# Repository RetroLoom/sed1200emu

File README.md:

# SED1200Emu
This Emulator is intended to replace hard-to-obtain Epson SED1200 based LCD modules with common HD44780 ones. The original project page can be found here http://sensi.org/~tnt23/sed1200emu/index.html. The original goal is for having a replacement LCD for the Roland MT-32, but the display could be adapted for other projects. All attempts to reach the original designer have failed. Please reach out to me if you have any information about this. 

## Building and Installation
The main driver and translator for this project is an ATMEGA8L-8AU which can still be purchased on popular sites like Mouser and Digi-key. This IC may become obsolete, so the intention is to adapt as they become less available. The gerber files, BOM, Binary HEX files will also be provided as they become current and available. All current releases are in beta, and come with no warranty. 

### ATMEGA8 Flashing
When programming the ATMEGA8 it is important to use the correct configuration. This will enable the external clocks and any other flags needed for binary to run correctly. 

Fuse Low Byte: 0xBF

Fuse High Bte: 0xD9

Lock Bit Byte: 0xFF

### Compiling
Download and install WinAVR for minimum compiling support. Using command prompt or windows powershell, run make in the src directory.

Note: You can optionally replace the AVR compiling files to manually update to newer versions. 

### UART Config
For debugging or logging display message, connect via serial to GND, TXD, RXD at 9600 baud.

UART Serial out display clone (and debugging).

### Optional Headers
There are three headers that are considered optional, but recommended if you are developing or want to reprogram the ATMEGA8 after it is soldered to the board. The SPI header will provide connection for flashing, and the UART header will give you access to feedback and debug information for code development. 

## Development Notes
At the moment, 20x2 HD44780 LCD is too large as a direct replacement for the MT-32. Adaptation will be needed in the form of a redesigned 3D printed face plate for the current LCD. If you have interest in helping design something like this, please get in touch! I have searched around for better fitting 20x2 LCD's but I have not found anything that would match. 

Another option is to program new methods that adapts the display to a 16x2 LCD. This might need some elaborate programming to work. 

## License Information
The original release this project is derived from Tim Tashpulatov without license or warranty. The updated revisions of this project released in 2024 include a GPL v3 license which can be found here in the LICENSE file. 

Source code and software license - [GPL v3](https://github.com/skadarnold/sed1200emu/blob/master/LICENSE)

Hardware design license - [CERN OHL-S](https://ohwr.org/project/cernohl/-/wikis/uploads/819d71bea3458f71fba6cf4fb0f2de6b/cern_ohl_s_v2.txt)

## Support the Developer
This project is brought to you free and open source, but it is not free to develop. If you like this project please consider supporting this and future developments. 

https://www.patreon.com/RetroLoom

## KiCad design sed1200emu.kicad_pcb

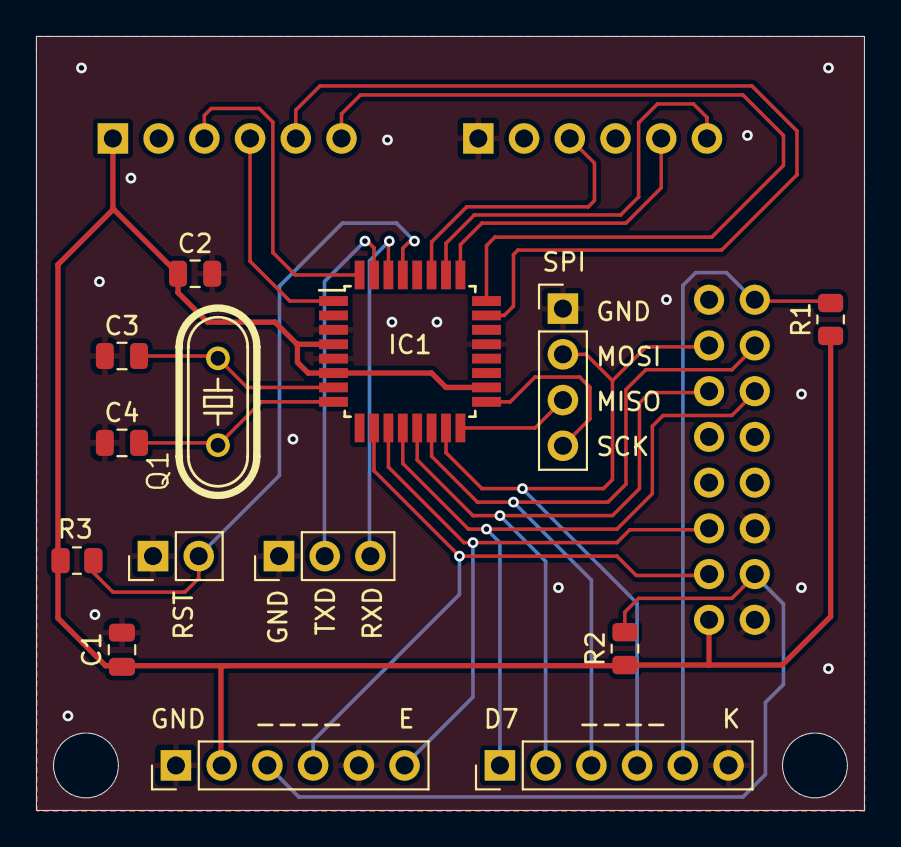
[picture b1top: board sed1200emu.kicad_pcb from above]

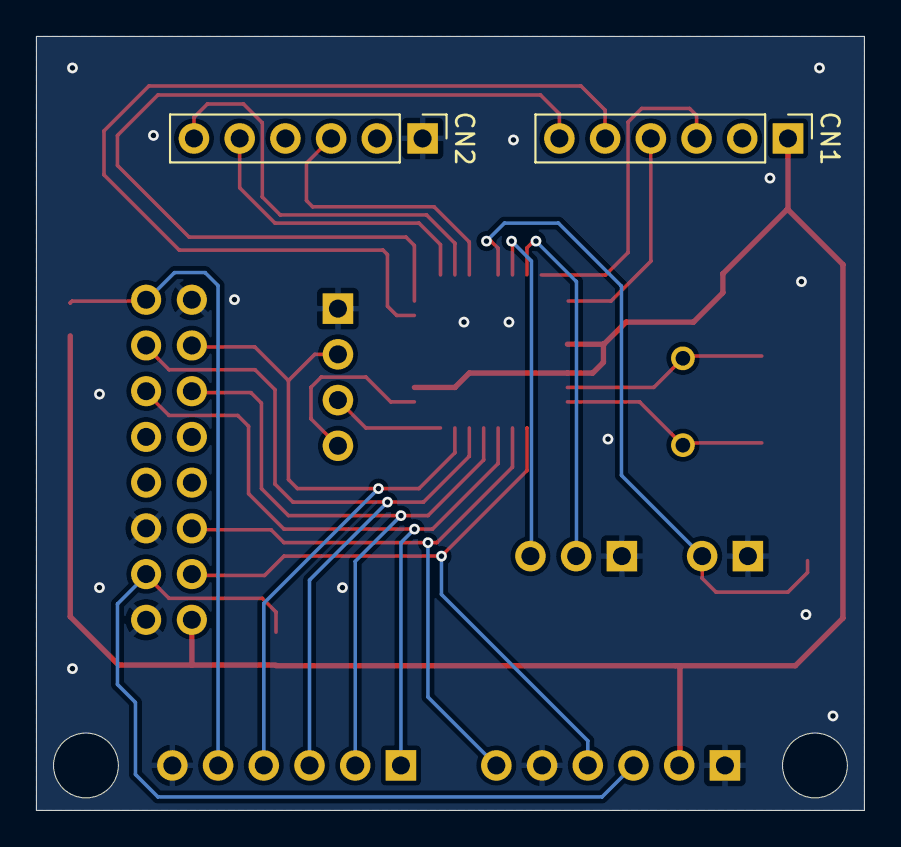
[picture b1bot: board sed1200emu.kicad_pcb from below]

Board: 2 copper layers, 46.0 x 43.0 mm, 17 parts (2 on the bottom side), 24 nets.

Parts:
C1, C2: 0.1uF; C_0805_2012Metric
C3, C4: 22p; C_0805_2012Metric
CN1, CN2: Conn_01x06_Pin 2.54mm; PinHeader_1x06_P2.54mm_Vertical
DIS1: SMH2002-A; TUXGR_20X2
DIS2-1, DIS2-2: Conn_01x06_Pin; PinHeader_1x06_P2.54mm_Vertical
IC1: ATMEGA8L-8AU; TQFP-32_7x7mm_P0.8mm
Q1: HC-49/S 16pF; HC49_S
R1, R2: 330; R_0805_2012Metric
R3: 10k; R_0805_2012Metric
RESET1: Conn_01x02_Pin; PinHeader_1x02_P2.54mm_Vertical
SPI1: Conn_01x04_Pin; PinHeader_1x04_P2.54mm_Vertical
UART1: Conn_01x03_Pin; PinHeader_1x03_P2.54mm_Vertical

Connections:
/ADC0: CN1.5, IC1.23 (PC0(ADC0))
/ADC1: CN1.6, IC1.24 (PC1(ADC1))
/ADC2: CN2.5, IC1.25 (PC2(ADC2))
/ADC3: CN2.6, IC1.26 (PC3(ADC3))
/ADC4: CN2.3, IC1.27 (PC4(ADC4/SDA))
/AIN0: DIS1.4 (RS), DIS2-1.4, IC1.10 (PD6(AIN0))
/AIN1: DIS1.6 (E), DIS2-1.6, IC1.11 (PD7(AIN1))
/ICP: DIS1.11 (D4), DIS2-2.1, IC1.12 (PB0(ICP))
/INT0: CN1.3, IC1.32 (PD2(INT0))
/INT1: CN1.4, IC1.1 (PD3(INT1))
/LCD_A: DIS1.15 (LED_A), DIS2-2.5, R1.2
/LCD_CONTR: DIS1.3 (CONTR), DIS2-1.3, R2.2
/LCD_D5: DIS1.12 (D5), DIS2-2.2, IC1.13 (PB1(OC1A))
/LCD_D6: DIS1.13 (D6), DIS2-2.3, IC1.14 (PB2(SS/OC1B))
/LCD_D7: DIS1.14 (D7), DIS2-2.4, IC1.15 (PB3(MOSI/OC2)), SPI1.2
/MISO: IC1.16 (PB4(MISO)), SPI1.3
/RXD: IC1.30 (PD0(RXD)), UART1.3
/SCK: IC1.17 (PB5(SCK)), SPI1.4
/TXD: IC1.31 (PD1(TXD)), UART1.2
GND: C1.2, C2.2, C3.1, C4.1, CN2.1, DIS1.1 (GND), DIS1.5 (R/W), DIS1.16 (LED_K), DIS2-1.1, DIS2-1.5, DIS2-2.6, IC1.3 (GND@1), IC1.5 (GND@2), IC1.21 (GND), RESET1.1, SPI1.1, UART1.1
unnamed: C3.2, IC1.7 (PB6(XTAL1/TOSC1)), Q1.2
unnamed: C4.2, IC1.8 (PB7(XTAL2/TOSC2)), Q1.1
unnamed: IC1.29 (PC6(/RESET)), R3.1, RESET1.2
VCC: C1.1, C2.1, CN1.1, DIS1.2 (VCC), DIS2-1.2, IC1.4 (VCC@1), IC1.6 (VCC@2), IC1.18 (AVCC), R1.1, R2.1, R3.2

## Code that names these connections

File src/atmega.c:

/*
 * This file is part of the SED1200EMU Project.
 *
 * SED1200EMU is free software: you can redistribute it and/or modify
 * it under the terms of the GNU General Public License as published by
 * the Free Software Foundation, either version 3 of the License, or
 * (at your option) any later version.
 *
 * This program is distributed in the hope that it will be useful,
 * but WITHOUT ANY WARRANTY; without even the implied warranty of
 * MERCHANTABILITY or FITNESS FOR A PARTICULAR PURPOSE. See the
 * GNU General Public License for more details.
 *
 * You should have received a copy of the GNU General Public License
 * along with this program. If not, see <https://www.gnu.org/licenses/>.
 */

#include <avr/io.h>
#include <avr/interrupt.h>
#include <util/delay.h>

#include <string.h>
#include <stdio.h>
#include <stdlib.h>
#include <stdint.h>

#include "atmega.h"
#include "lcd.h"
#include "tables.h"
#include "uart.h"

uint8_t xlat [16] = {
	0b0000, 0b1000, 0b0010, 0b1010,
	0b0100, 0b1100, 0b0110, 0b1110,
	0b0001, 0b1001, 0b0011, 0b1011,
	0b0101, 0b1101, 0b0111, 0b1111
};

volatile uint8_t sed_byte;
volatile uint8_t rs;
volatile uint8_t count_e;

volatile uint32_t millis = 0; // Millisecond counter, volatile because it's modified in ISR

void ATMEGA_Init()
{
    // PORT B
	// ---------------------------
	// PB3		(LCD) D7		o
	// PB2		(LCD) D6		o
	// PB1		(LCD) D5		o
	// PB0		(LCD) D4		o

	DDRB =	0xF;

	// PORT C
	// ---------------------------
	// PC4		(SED1200) RS	i
	// PC3		(SED1200) D0	i
	// PC2		(SED1200) D2	i
	// PC1		(SED1200) D1	i
	// PC0		(SED1200) D3	i

	DDRC = 0;

	// PORT D
	// --------------------------
	// PD7		(LCD) E			o
	// PD6		(LCD) RS 		o
	// PD3		(SED1200) E 	i aka INT1
	// PD2		(SED1200) CS 	i aka INT0

	DDRD = 0xC0;

	MCUCR = _BV(ISC11) | _BV(ISC10) |		// 11 - INT1 rising edge
			_BV(ISC01);						// 10 - INT0 falling edge

	GICR = _BV(INT1) | _BV(INT0);			// enable INT1 and INT0

    //Timer0_Init();
	Timer1_Init();
	//Timer2_Init();

    sei ();
}

void Timer0_Init() {
    // Timer0 Configuration for Compare Match mode
    OCR0 = 249;  // Set the compare match value (adjust as needed)
    TCCR0 = (1 << WGM01) | (1 << CS02) | (1 << CS00);  // CTC mode, prescaler clk/1024
    TIMSK |= (1 << OCIE0);  // Enable Timer0 compare match interrupt
}

void Timer1_Init() {
    /* Set up Timer1 for 1 ms overflow
    TCCR1A = 0;                     // Set Timer1 to normal mode
    TCCR1B = (1 << WGM12) | (1 << CS11); // CTC mode, prescaler of 8
    OCR1A = 999;                    // Output compare match value for 1ms at 8 MHz/8 prescaler
    TIMSK = (1 << OCIE1A);         // Enable output compare A match interrupt
	*/

	// Set up Timer1 for direct updateDisplay()
	TCCR1B |= (1 << WGM12);      // Configure Timer1 in CTC mode
    TCCR1B |= (1 << CS11) | (1 << CS10); // Set prescaler to 64
    OCR1A = 12500;               // Set compare value for 100 ms interval
    TIMSK |= (1 << OCIE1A);      // Enable Timer1 compare match A interrupt
	//

	/* Set up Timer1 for a 1-second interval
	TCCR1A = 0;				// Set Timer1 to normal mode (CTC)
	TCCR1B |= (1 << WGM12); // Configure Timer1 in CTC mode
	TCCR1B |= (1 << CS12);	// Set prescaler to 256
	OCR1A = 31249;			// Compare value for 1 second interval at 8 MHz / 256 prescaler
	TIMSK |= (1 << OCIE1A); // Enable Timer1 compare match A interrupt
	*/
}

void Timer2_Init() {
	// Set up Timer2 for 1ms overflow (8-bit timer)
	TCCR2 = (1 << WGM21) | (1 << CS21); // CTC mode, prescaler of 8
	OCR2 = 249;							// Output compare match value for 1ms at 8 MHz/8 prescaler
	TIMSK |= (1 << OCIE2);				// Enable output compare A match interrupt
}

//ISR(TIMER0_COMPA_vect) 
//{
        
        /*
		lcdIdx ++;
		
		if (lcdIdx >= 40)
			lcdIdx = 0;

		if (lcdIdx == 0)
			LCD_SendCmd (0x80);

		if (lcdIdx == 20)
			LCD_SendCmd (0xc0);
		*/

		//LCD_SendChar (LCDBuffer [lcdIdx]);
		
		//updateDisplay();
//}

// Timer1 compare match ISR, triggers every 1 ms
ISR(TIMER1_COMPA_vect) {
    millis += 100;
    //updateDisplay();
}

//ISR(TIMER2_COMPA_vect) {
//    millis++;
//}

ISR(INT0_vect) {
	count_e = 0;
}

ISR(INT1_vect) {
	//sei ();
	

	if (!(count_e & 0x01)) {
		// upper data D7...D4
		sed_byte = xlat [(PINC & 0x0f)] << 4;
	}
	else {
		// lower data D3...D0
		sed_byte |= xlat [(PINC & 0x0f)];
		rs = PINC & _BV(PC4);		

		if (rs) {
			// data
			LCD_Enqueue (sed_byte);
		}
		else {
			// command
			switch (sed_byte & 0xc0) {				
				case 0x80:
					LCD_Enqueue (sed_byte);
					break;
				case 0xc0:
					LCD_Enqueue (0x80 + 10 + (sed_byte & 0x3f));
					break;
				default:
					break;

			}

//			if ((sed_byte & 0xc0) == 0x80) {	// SET CURSOR ADDR
//				LCD_Enqueue (sed_byte);
//			}
		}	
	}

	count_e ++;
	
}

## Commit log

2024-10-12 sed1200emu Init
2024-10-12 Change TUXGR_20X2 Mask / Through hole cuts to User Drawings
2024-10-12 Replace MEGA8 Symbol and Footprint
2024-10-12 Replace CN1 and CN2 with KiCad Symbols
2024-10-12 Replace all 1pin out headers to KiCad Symbols
2024-10-12 Net class trace changes
2024-10-12 Update 20X2 Display Symbol & and fix pin header references
2024-10-12 Clean trace and connections
2024-10-12 Fix Clearance and Design Rule Violations
2024-10-12 Fix all TUXGR_20X2 Silkscreen/ Cuts to User Layer
2024-10-12 Fix more Rule Violations
2024-10-12 Add Ground Vias
2024-10-12 Update Reference Values for BOM
2024-11-08 Working SED1200EMU
2024-11-08 More cleanup, ATMEGA.c
2024-11-08 Add HEX File
2024-11-08 Makefile and compile changes
2024-11-08 Clean up code and LCD Initialization process, add SendStr and ScrollStr, MT32 startup message
2024-11-08 SEDBuffer, Hex Tables, Cleanup
2024-11-08 Remove original source zip
2024-11-09 Experimental Section Triggers
    None of this is working the way I was expecting, so I am ditching it. However I would like to save my work in a commit in case I ever need to refer back to it for some reason.
2024-11-09 Initial sectioning and timer
2024-11-09 Cleanup Experimental Section Display
2024-11-09 bufferDisplay Flag
2024-11-10 Cleanup PCB, Add UART header, Consolidate SPI headers, Reset VCC Connect
2024-11-10 Cleanup edge cuts and fill zones
2024-11-10 Add standoff holes for bottom support
2024-11-11 Added single row HD44780 header, shifted all components up to make better use of space
2024-11-19 Add gerber files
2024-11-19 Fix README typo
2024-12-05 Update Binary HEX
2024-12-05 Configure UART
2024-12-05 Display Debug Output
2024-12-05 Update Binary HEX for UART
2024-12-05 Update README and Images
2024-12-05 Add GPL v3 License
2024-12-05 Update with hardware license
2024-12-07 Expand and enhance UART
    Terminal clones display of the MT32. Raised baud rate for smoother refreshing rates. Debug mode for log mode.
2024-12-07 Update terminal display image
2024-12-07 UART Display clean up and bug fixes, limit character display to < 20
2024-12-07 Update terminal display image and README
2024-12-07 UART Receive on vector, receiving updates, fix vertical bar
2024-12-07 Ignore putty.log in src directory
